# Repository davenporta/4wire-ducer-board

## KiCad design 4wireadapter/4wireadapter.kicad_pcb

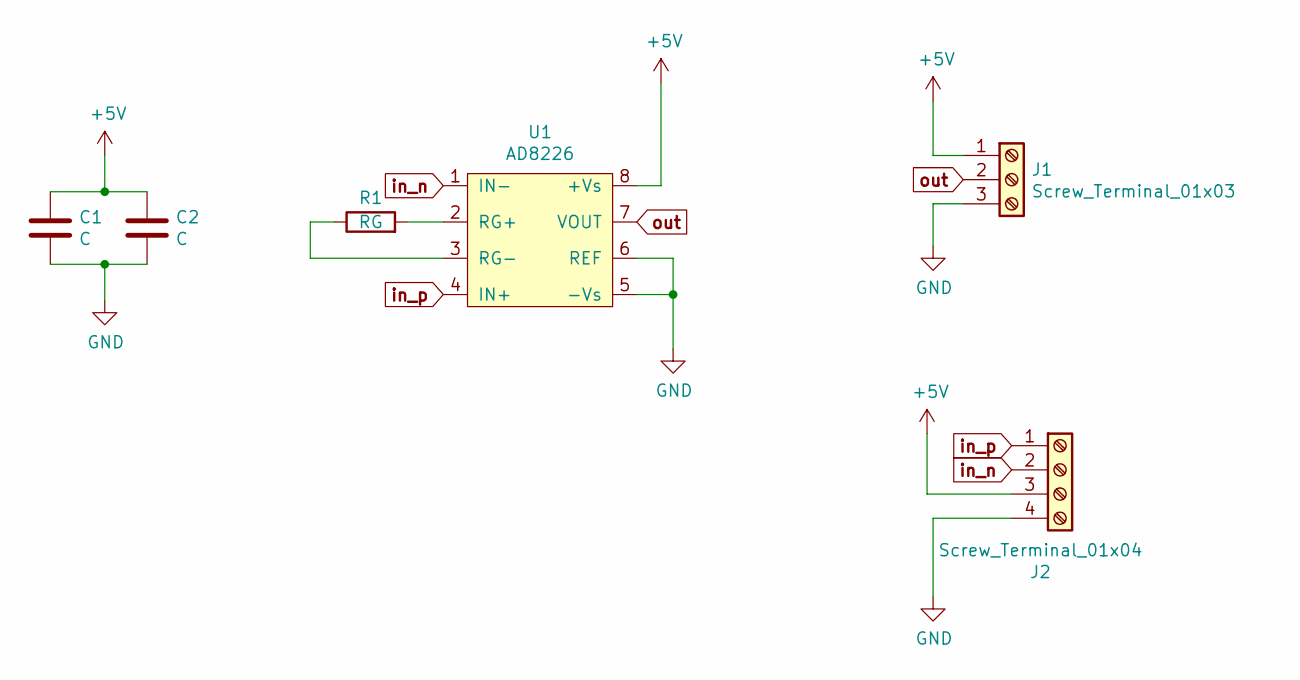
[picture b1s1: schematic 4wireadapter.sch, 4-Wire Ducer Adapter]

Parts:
C1, C2: C; C_0603_1608Metric
J1: Screw_Terminal_01x03; TerminalBlock_bornier-3_P5.08mm
J2: Screw_Terminal_01x04; TerminalBlock_bornier-4_P5.08mm
R1: RG; R_0603_1608Metric
U1: AD8226; SOIC-8_3.9x4.9mm_P1.27mm

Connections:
+5V: C1.1, C2.1, J1.1, J2.3, U1.8 (+Vs)
GND: C1.2, C2.2, J1.3, J2.4, U1.5 (-Vs), U1.6 (REF)
unnamed: R1.1, U1.3 (RG-)
unnamed: R1.2, U1.2 (RG+)
in_n: J2.2, U1.1 (IN-)
in_p: J2.1, U1.4 (IN+)
out: J1.2, U1.7 (VOUT)

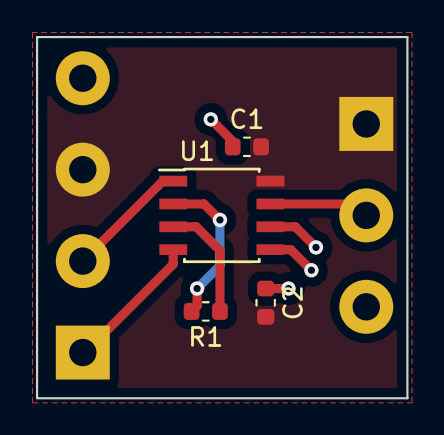
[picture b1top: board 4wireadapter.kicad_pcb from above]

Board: 2 copper layers, 20.6 x 20.1 mm, 6 parts (0 on the bottom side), 7 nets.

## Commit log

2021-07-20 rev 2 sent for fab
